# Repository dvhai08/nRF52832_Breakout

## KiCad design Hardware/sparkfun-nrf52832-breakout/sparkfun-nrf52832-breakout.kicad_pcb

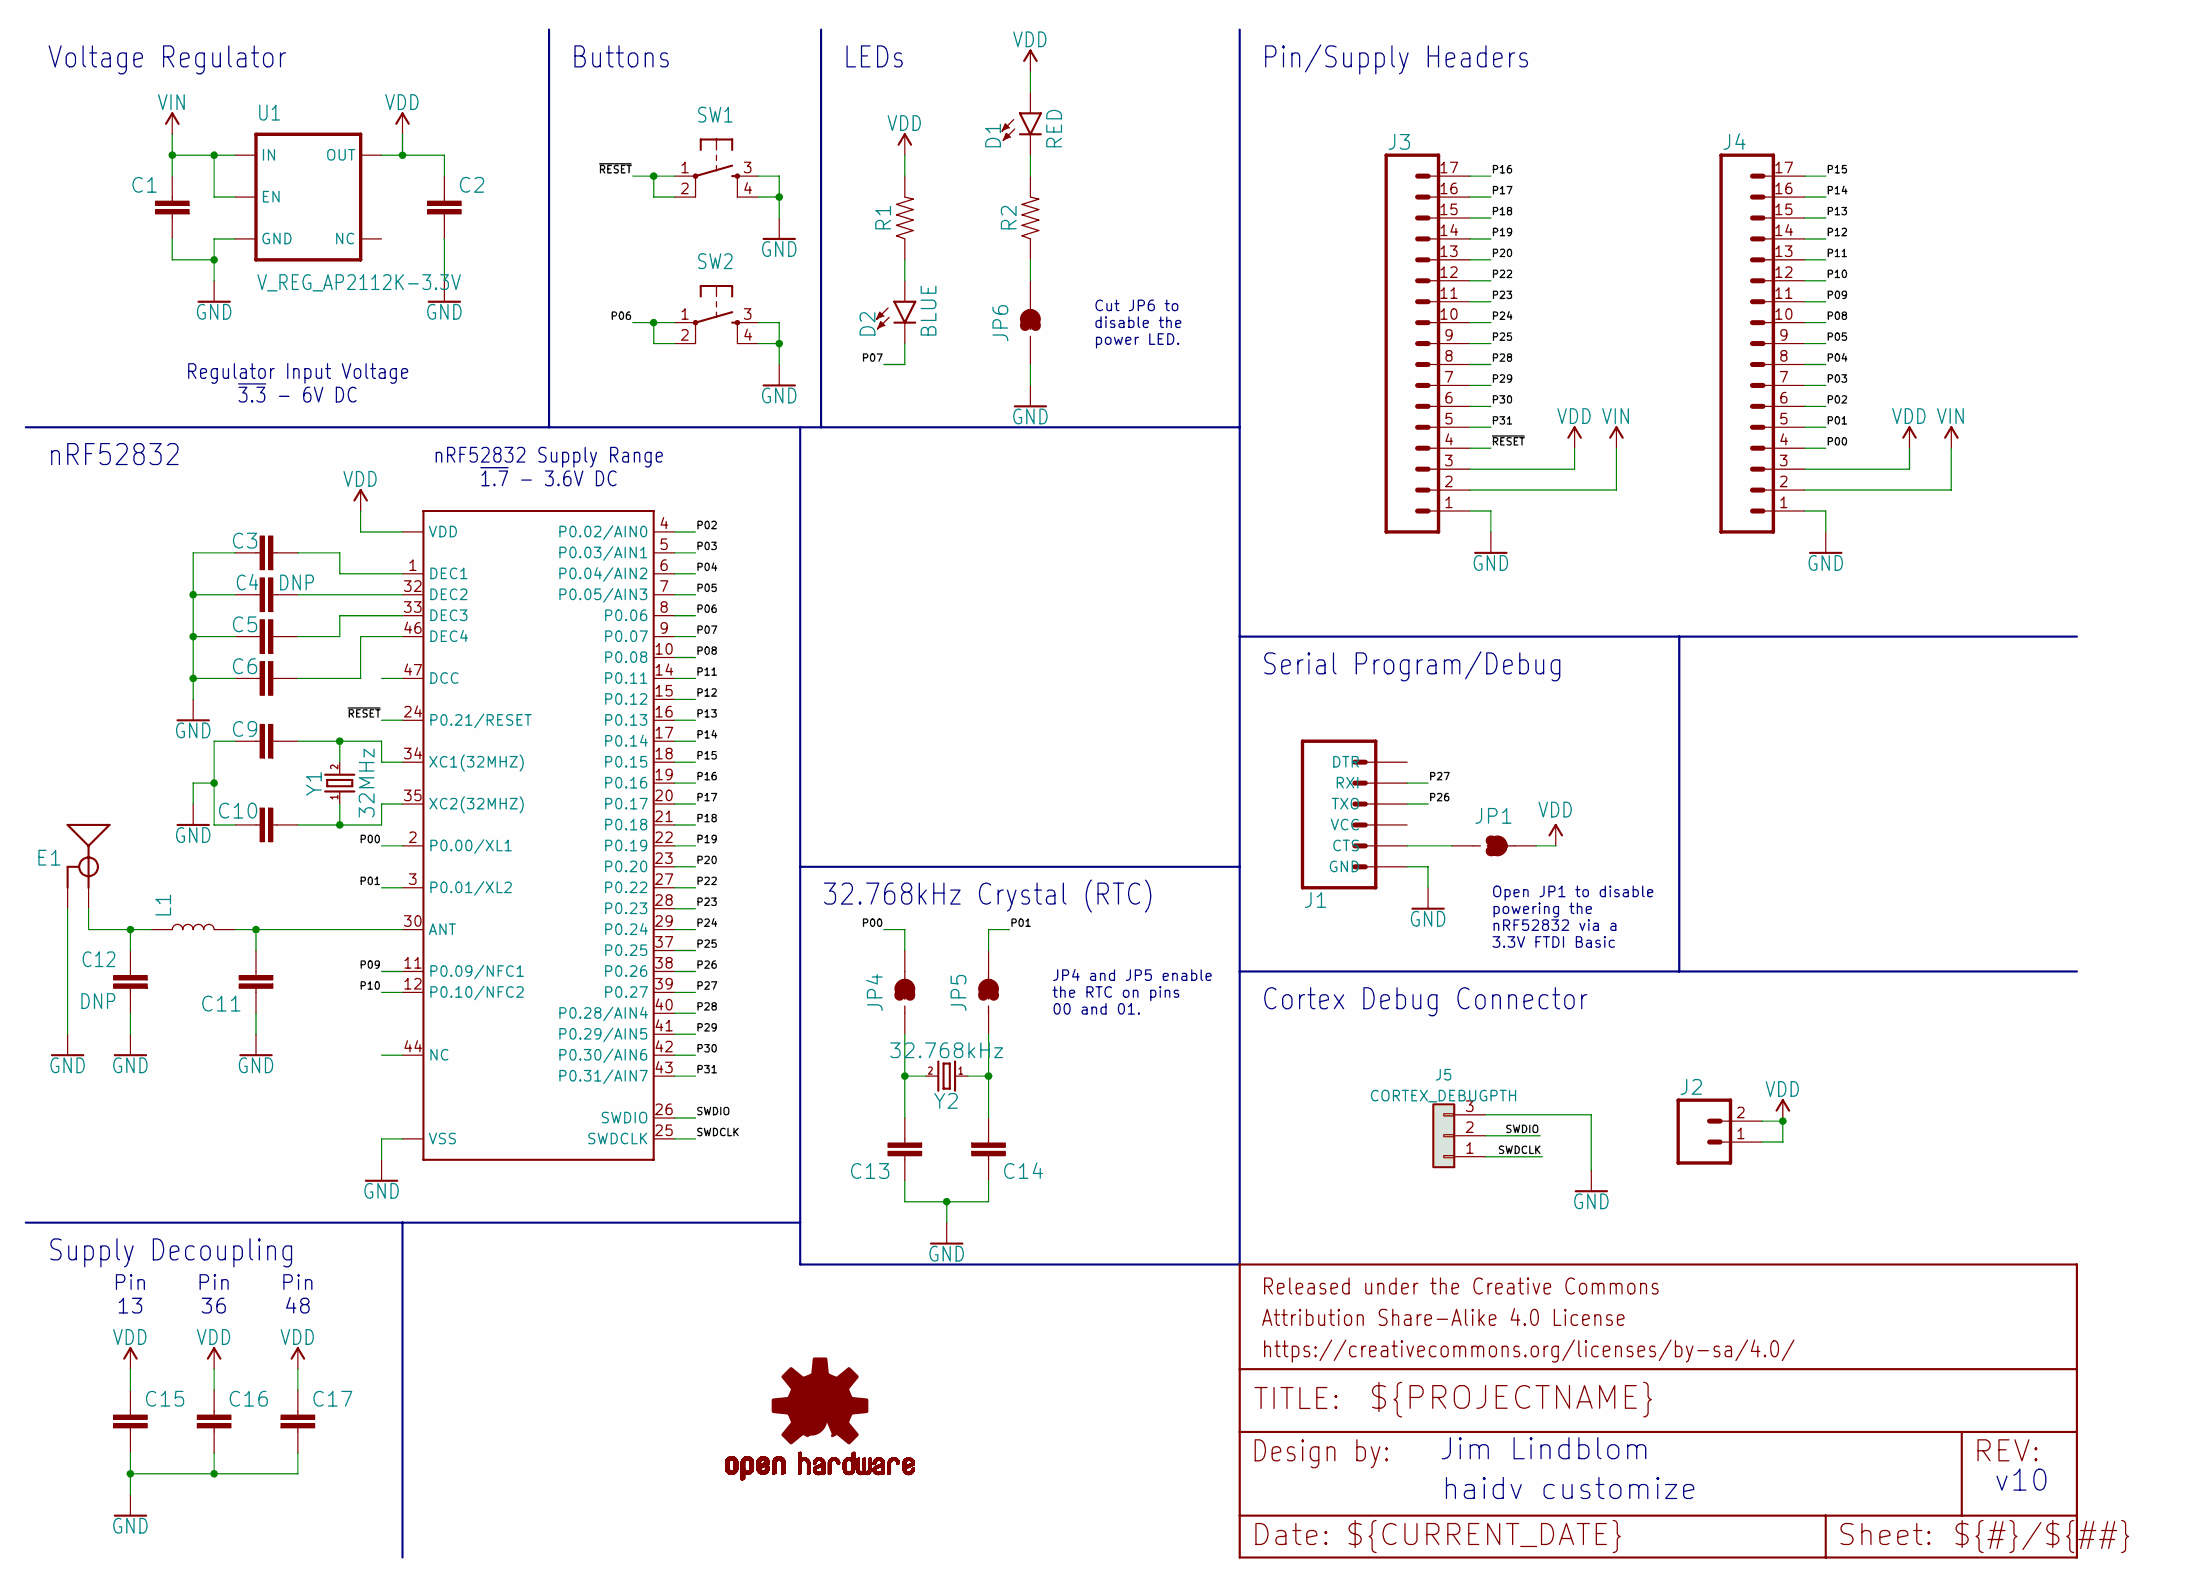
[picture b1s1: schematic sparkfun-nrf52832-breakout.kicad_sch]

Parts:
C1: 1.0UF-0603-16V-10%; 0603
C2: 2.2UF-0603-10V-20%; 0603
C3, C15, C16: 0.1UF-0402-16V-10%; C_0402_1005Metric
C4: DNP; C_0402_1005Metric
C5: 100PF-0402-50V-5%; C_0402_1005Metric
C6: 1.0UF-0402-16V-10%; C_0402_1005Metric
C9, C10: 6PF-0402-50V-0.5%; C_0402_1005Metric
C11: 0.8PF-0402-50V-0.1PF; C_0402_1005Metric
C12: DNP; 0402
C13, C14: 15PF-0402-50V-5%; C_0402_1005Metric
C17: 4.7UF0603; C_0603_1608Metric
D1: RED; LED-0603
D2: BLUE; LED-0603
E1: ANTENNA-GROUNDEDTRACE-15.2MM; TRACE_ANTENNA_2.4GHZ_15.2MM
FRAME1: FRAME-LETTER; CREATIVE_COMMONS
J1: ARDUINO_SERIAL_PROGRAMPTH; 1X06
J2: CONN_02PTH; 1X02
J3, J4: CONN_17; 1X17
J5: CORTEX_DEBUGPTH; PinHeader_1x03_P2.54mm_Vertical
JP1, JP4, JP5, JP6: JUMPER-PAD-2-NC_BY_TRACE; PAD-JUMPER-2-NC_BY_TRACE_YES_SILK
L1: INDUCTOR-0402-3.9NH; 0402
LOGO1: OSHW-LOGOMINI; OSHW-LOGO-MINI
R1, R2: 1KOHM-0603-1/10W-1%; 0603
SW1, SW2: TACTILE_SWITCH_SMD_4_6X2_8MM; TACTILE_SWITCH_SMD_4.6X2.8MM
U1: V_REG_AP2112K-3.3V; SOT23-5
U2: NRF52832; QFN48-6X6MM
Y1: 32MHz; CRYSTAL-SMD-2.0X1.6MM
Y2: 32.768kHz; CRYSTAL-SMD-3.2X1.5MM

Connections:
/P00: J4.4, JP4.2, U2.2 (P0.00/XL1)
/P01: J4.5, JP5.2, U2.3 (P0.01/XL2)
/P02: J4.6, U2.4 (P0.02/AIN0)
/P03: J4.7, U2.5 (P0.03/AIN1)
/P04: J4.8, U2.6 (P0.04/AIN2)
/P05: J4.9, U2.7 (P0.05/AIN3)
/P06: SW2.1, SW2.2, U2.8 (P0.06)
/P07: D2.C, U2.9 (P0.07)
/P08: J4.10, U2.10 (P0.08)
/P09: J4.11, U2.11 (P0.09/NFC1)
/P10: J4.12, U2.12 (P0.10/NFC2)
/P11: J4.13, U2.14 (P0.11)
/P12: J4.14, U2.15 (P0.12)
/P13: J4.15, U2.16 (P0.13)
/P14: J4.16, U2.17 (P0.14)
/P15: J4.17, U2.18 (P0.15)
/P16: J3.17, U2.19 (P0.16)
/P17: J3.16, U2.20 (P0.17)
/P18: J3.15, U2.21 (P0.18)
/P19: J3.14, U2.22 (P0.19)
/P20: J3.13, U2.23 (P0.20)
/P22: J3.12, U2.27 (P0.22)
/P23: J3.11, U2.28 (P0.23)
/P24: J3.10, U2.29 (P0.24)
/P25: J3.9, U2.37 (P0.25)
/P26: J1.3 (TXO), U2.38 (P0.26)
/P27: J1.2 (RXI), U2.39 (P0.27)
/P28: J3.8, U2.40 (P0.28/AIN4)
/P29: J3.7, U2.41 (P0.29/AIN5)
/P30: J3.6, U2.42 (P0.30/AIN6)
/P31: J3.5, U2.43 (P0.31/AIN7)
/SWDCLK: J5.1, U2.25 (SWDCLK)
/SWDIO: J5.2, U2.26 (SWDIO)
/~RESET: J3.4, SW1.1, SW1.2, U2.24 (P0.21/RESET)
GND: C1.2, C2.2, C3.1, C4.1, C5.1, C6.1, C9.1, C10.2, C11.1, C12.2, C13.1, C14.1, C15.2, C16.2, C17.2, E1.GND, J1.6 (GND), J3.1, J4.1, J5.3, JP6.1, SW1.3, SW1.4, SW2.3, SW2.4, U1.2 (GND), U2.31 (VSS), U2.45 (VSS), U2.EP (VSS)
unnamed: D1.C, R2.2
unnamed: D2.A, R1.1
unnamed: C12.1, E1.ANT (SIGNAL), L1.1
unnamed: J1.5 (CTS), JP1.1
unnamed: JP6.2, R2.1
unnamed: C11.2, L1.2, U2.30 (ANT)
unnamed: C3.2, U2.1 (DEC1)
unnamed: C4.2, U2.32 (DEC2)
unnamed: C5.2, U2.33 (DEC3)
unnamed: C6.2, U2.46 (DEC4)
unnamed: C9.2, U2.34 (XC1(32MHZ)), Y1.3 (2)
unnamed: C10.1, U2.35 (XC2(32MHZ)), Y1.1
unnamed: C14.2, JP5.1, Y2.P$1 (1)
unnamed: C13.2, JP4.1, Y2.P$2 (2)
VDD: C2.1, C15.1, C16.1, C17.1, D1.A, J2.1, J2.2, J3.3, J4.3, JP1.2, R1.2, U1.5 (OUT), U2.13 (VDD), U2.36 (VDD), U2.48 (VDD)
VIN: C1.1, J3.2, J4.2, U1.1 (IN), U1.3 (EN)

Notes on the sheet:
Pin 36
nRF52832 Supply Range ~{1.7} - 3.6V DC~{}
haidv customize
v10
32.768kHz Crystal (RTC)
Cortex Debug Connector
Pin 13
LEDs
Jim Lindblom
Pin 48
Open JP1 to disable powering the nRF52832 via a 3.3V FTDI Basic
Serial Program/Debug
Supply Decoupling
Buttons
Pin/Supply Headers
JP4 and JP5 enable the RTC on pins 00 and 01.
Cut JP6 to disable the power LED.
nRF52832
Voltage Regulator
Regulator Input Voltage ~{3.3} - 6V DC~{}

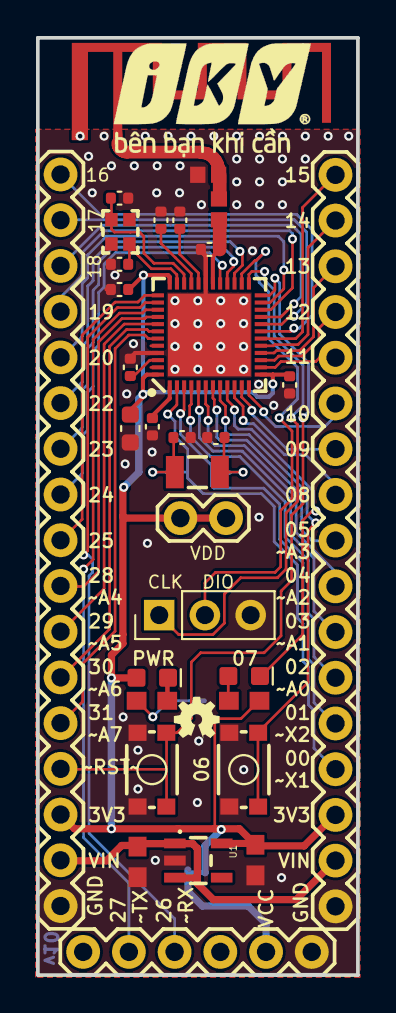
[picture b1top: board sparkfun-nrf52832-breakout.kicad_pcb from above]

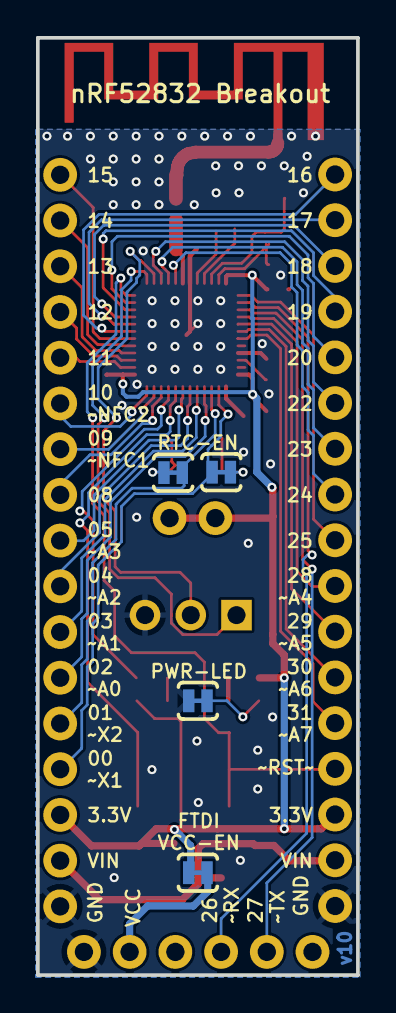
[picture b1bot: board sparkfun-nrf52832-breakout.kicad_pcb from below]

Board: 2 copper layers, 17.8 x 52.1 mm, 38 parts (4 on the bottom side), 51 nets.

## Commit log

2023-04-22 new create

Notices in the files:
Hardware/sparkfun-nrf52832-breakout/sparkfun-nrf52832-breakout.kicad_sch:
https://creativecommons.org/licenses/by-sa/4.0
Released under the Creative Commons
parts and their libraries:
Released under the Creative Commons Attribution Share-Alike 4.0 License
